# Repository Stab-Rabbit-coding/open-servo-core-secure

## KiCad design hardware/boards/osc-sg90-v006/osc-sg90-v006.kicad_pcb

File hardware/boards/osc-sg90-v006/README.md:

# OSC SG90 CH32

> ⚠️ **Designed, not spun. Pre-fabrication, pre-bringup.**
> This board has never been fabbed. Numbers and behaviour described below are **design intent**, not measured. The schematic and layout exist; firmware v2 now runs on the dev board (the bus transport is silicon-proven) but has never run on *this* board. Don't fab this without doing your own review first, and expect changes when bringup finally happens.

OpenServoCore swap board for SG90-class hobby servos. Compact, double-sided, designed to physically replace the factory PCB inside an SG90 case. CH32V006-based, single-wire TTL servo bus (osc-native protocol), drop-in mechanical fit.

## Overview

- **MCU** — CH32V006F8U6 (RISC-V, 48 MHz, 62 KB flash, 8 KB RAM).
- **Motor driver** — TI DRV8837 H-bridge (1.8 A peak, IN1/IN2 PWM).
- **LDO** — TPAP2210K-3.3, 3.3 V logic rail.
- **UART buffer** — SN74LVC1G07 open-drain for the half-duplex TTL bus.
- **Current shunt** — 25 mΩ, 1 % on the low side.
- **Power input** — 3.3-8.4 V (1S-2S LiPo) via the servo cable.
- **Debug** — 4-pad SWD interface for WCH-LinkE.
- **Position feedback** — existing servo potentiometer wiper.
- **Form factor** — 10 × 12.5 mm, double-sided assembly.
- **Secure element** — Microchip ECC204 (`U7`), 8-pad UDFN package, SWI on
  `PD6` [REF-SE-001]. **Placed on B.Cu with a generic 3D proxy model; 2
  residual real DRC clearance conflicts still open** — see
  [Secure element](#secure-element) below and `TODO.md` §7.8.

## Connectors

### Servo cable — J1 (1×3, through-hole pads)

Standard hobby-servo 3-wire pinout, but the signal pin carries half-duplex UART instead of PWM:

| Pin | Net    | Notes                                   |
| --- | ------ | --------------------------------------- |
| 1   | `VIN`  | 3.3-8.4 V (1S-2S LiPo).                 |
| 2   | `DATA` | Half-duplex UART, baud TBD by firmware. |
| 3   | `GND`  |                                         |

### Motor — J2 (2 wire pads)

Solder directly to the SG90 motor leads.

| Pad    | Net              |
| ------ | ---------------- |
| `OUTA` | Motor terminal A |
| `OUTB` | Motor terminal B |

### Potentiometer — J3 (3 pads)

Connects to the existing servo potentiometer.

| Pad    | Net          |
| ------ | ------------ |
| `+3V3` | Pot top rail |
| `VPOS` | Wiper        |
| `GND`  | Pot ground   |

### Debug — J4 (4 pads, 1.27 mm pitch)

Single-wire SWD for WCH-LinkE. Programmed via `wlink` / `probe-rs`. Firmware build instructions land when firmware v2 starts; until then there's nothing to flash.

| Pad | Net     |
| --- | ------- |
| 1   | `+3V3`  |
| 2   | `GND`   |
| 3   | `SWDIO` |
| 4   | `NC`    |

## Design intent

These are the targets the board was laid out around. None are measured.

- **Power architecture** — VIN routes to the DRV8837 directly; 3.3 V logic rail off the TPAP2210K LDO. Bulk capacitance is 2× 10 µF on VIN. PGND/GND joined at a single net tie.
- **Position sensing** — 12-bit ADC on `VPOS` with an RC filter (10 kΩ + 100 nF, fc ≈ 160 Hz) to suppress wiper noise. Sub-degree resolution is the design goal; actual precision waits on bringup and firmware oversampling.
- **Voltage sensing** — 20 kΩ / 10 kΩ dividers (ratio 0.333) on `VINS`, `VSNA`, `VSNB`. 8.4 V → 2.8 V at the ADC.
- **Current sensing** — 25 mΩ low-side shunt, sized for the DRV8837's ~1.76 A peak via `R_shunt ≈ 44 mV / I_stall`, so the hardware stall-detect path trips near the driver's max output. Raw V_shunt = 25 mV at 1 A; firmware sets ADC sampling, gain path, and software overcurrent threshold.
- **Communication** — single-wire half-duplex TTL servo bus (Dynamixel-TTL electrical layer; the wire protocol is [osc-native](../../../docs/osc-native-protocol.md)). The SN74LVC1G07 open-drain buffer enables bidirectional comms over the single `DATA` line. Bus rates: 0.5-3 Mbaud, default 1 M.
- **Protection** — PESD5V0L1UL TVS on `DATA`.

## Secure element

`U7` is a Microchip ECC204 (Value `ECC204-MAVCZ-T`), **8-pad UDFN** package,
100 kbps PWM Single-Wire Interface (SWI). Design of record:
[`docs/security-architecture.md`](../../../docs/security-architecture.md);
citations: [`REFERENCES.md`](../../../REFERENCES.md) `REF-SE-001`.

| Signal | Net       | Notes                                                                   |
| ------ | --------- | ----------------------------------------------------------------------- |
| `SI/O` | `SE_SWIO` | `PD6` on the MCU, one pull-up (`R10`) to `+3V3`.                        |
| `VCC`  | `+3V3`    | 0.1 µF decoupling (`C5`).                                               |
| `GND`  | `GND`     | Also `EP` (pin 9, exposed pad) — REF-SE-001 recommends tying it to GND. |

**Package: 8-pad UDFN, not 3-Lead Contact.** The 3-Lead Contact package
(6.5×2.5 mm) — the original choice — was confirmed by exhaustive search to
have **zero** clear placement anywhere on this board's routed copper. The
same real part's 8-pad UDFN (2×3 mm) does fit; see `TODO.md` §7.8 for the
search methodology and REFERENCES.md's "Removed / superseded citations" for
the supersession record.

**Placement — on B.Cu, real position, 2 residual real DRC conflicts open:**

- `U7 (101.7, 93.4)`, `R10 (103.3, 92.4)`, `C5 (103.0, 97.1)`, `C10 (103.7,
  95.015, −90)`, `RS1 (105.245002, 96.755, 90)`, `C2 (108.18, 91.08)`, all
  B.Cu — these are the final positions after re-verifying (and, for `RS1`/
  `C10`, wholesale-restoring) a round of manual GUI repositioning; see the
  data-integrity note below.
- `pcb drc --severity-all`: driven from 148 violations (induced by the
  original manual 3-Lead-Contact placement) down to 74 total / 27 new vs. a
  clean baseline. Of those 27: **2 are real** (`U7` pad 5 and `R10` pad 2
  each sit too close to one of `J4`'s three real through-hole pads —
  `(104.51, 92.0)` / `(103.06, 95.0)` / `(104.51, 98.0)`, confirmed via
  live Gerber `%TO.P,J4,n%` component-attribute flashes, not a stale-fill
  or duplicate-reference artifact; see `TODO.md` §7.8 for the placement
  math proving `U7` cannot clear both nearby `J4`/`J2` pads at once, and for
  fix options), 18 are `GND_POUR` zone-clearance findings now assessed as
  **likely real** (point-in-polygon tested against a live-exported Gerber's
  filled copper region — `U7`'s non-`GND` pads land inside the poured
  copper with no relief — though a live KiCad "Fill All Zones" + re-DRC is
  still the only fully conclusive check), and 3 are cosmetic
  `lib_footprint_mismatch` warnings (hand-authored footprint graphics vs. a
  full library re-import).
- `sch erc --severity-all`: 0 new violations (1 pre-existing, unrelated
  `DRV8837C` library-mismatch warning).
- **(BLOCKER for fab)** The 2 real conflicts need either further placement
  in a live KiCad GUI (this work was done headlessly, matching real pad
  geometry pulled from the raw `.kicad_pcb` and cross-checked against
  exported Gerbers — no substitute for actually seeing it), smaller pads
  still, or a justified DRC exclusion matching the `.kicad_pro`'s existing
  three exclusions for `J4`'s one-sided-TH quirk.

**Still open beyond placement:**

- `R10`'s pull-up value is `TBD`. The summary datasheet [REF-SE-001] has no
  application-circuit section and gives no recommended SWI pull-up; that
  needs the NDA datasheet or a CryptoAuthLib reference design (`TODO.md`
  §7.4).
- `ECC204-MAVCZ-T` is the **plain, unprovisioned** ordering code — a real
  example straight from [REF-SE-001] §7 (Product Identification System), not
  the fleet provisioning SKU. Whether fleet units ship pre-provisioned
  (TrustFLEX/TrustCUSTOM) or get provisioned from this raw part is still open
  (`TODO.md` §7.1/§7.5).
- The footprint,
  [`hardware/shared.pretty/ECC204_UDFN-8-1EP_L2.0-W3.0-P0.50-EP0.61x1.3mm.kicad_mod`](../../shared.pretty/ECC204_UDFN-8-1EP_L2.0-W3.0-P0.50-EP0.61x1.3mm.kicad_mod),
  deliberately uses smaller-than-generous pads (peripheral pads 0.5×0.25 mm,
  EP land 0.61 mm wide) to fit this board's real estate — sized to
  [REF-SE-001] §6.1's own terminal-to-exposed-pad `K = 0.20 mm` minimum, not
  arbitrary. Verify against a real part/stencil before fab.
- **Correction to a prior session's note:** an earlier pass here reported a
  "duplicate `J4` footprint / phantom pad" bug. That was wrong — it was a
  sign error in the reviewer's own PCB rotation math (`Rot(+θ)` used where
  `Rot(−θ)` was correct), not a board defect. `J4` is a single real
  footprint with three real through-hole pads; see `TODO.md` §7.8 for the
  corrected transform and its Gerber-based verification.
- **3D models added** for `U7`, `R10`, `C5` so KiCad's 3D viewer no longer
  shows bare footprints for these parts. `R10`/`C5` use the existing
  KiCad standard-library STEP models
  (`Resistor_SMD.3dshapes/R_0402_1005Metric.step`,
  `Capacitor_SMD.3dshapes/C_0402_1005Metric.step`), matching this board's
  existing convention for other passives. `U7` has no vendor-supplied
  3D model (Microchip does not publish one for the 8-pad UDFN), so it uses
  a generic dimensionally-accurate proxy generated from
  [REF-SE-001] §6.1's package dimensions (2.00 × 3.00 mm body, 0.55 mm
  height) — script and STL live at
  [`hardware/shared.3dshapes/ECC204_UDFN-8-1EP_L2.0-W3.0-P0.50.stl`](../../shared.3dshapes/ECC204_UDFN-8-1EP_L2.0-W3.0-P0.50.stl).
  Model references were added both to the library footprint
  (`shared.pretty/...kicad_mod`) and to each board instance directly (KiCad
  stores a full independent copy per instance — a library-only edit does
  not propagate to footprints already placed on this board). Confirmed no
  DRC regression from adding the models (74/9/27 unchanged); full visual
  confirmation in KiCad's 3D viewer was not achieved headlessly and should
  be spot-checked in the GUI before fab.
- **ERC/DRC verified with KiCad 10.0.3** (`kicad-cli` from the KiCad 10
  AppImage — the system-installed `kicad-cli` is 9.0.2 and cannot even load
  this file, since it's `generator_version "10.0"`).

## Assembly

Double-sided assembly, no vias-in-pads. Suitable for hot-plate / hot-air / IR reflow, or JLCPCB SMT. The board is 8-layer for routing density at this size.

## Mechanical fit

Designed to drop into a standard SG90 servo case:

- Motor leads solder to `OUTA` / `OUTB`.
- Pot wiper connects to `J3`.
- Servo cable connects to `J1`.
- Debug pads remain accessible through the case opening for bringup / reflashing.

Pad spacing for motor leads and debug pitch are still **to be confirmed against a physical case** when first boards arrive.

## License

Hardware files (schematic, layout, board files in this directory) are licensed under [CERN-OHL-P v2.0](../../../LICENSE-HARDWARE). See the [top-level README](../../../README.md#license) for the full licensing picture.

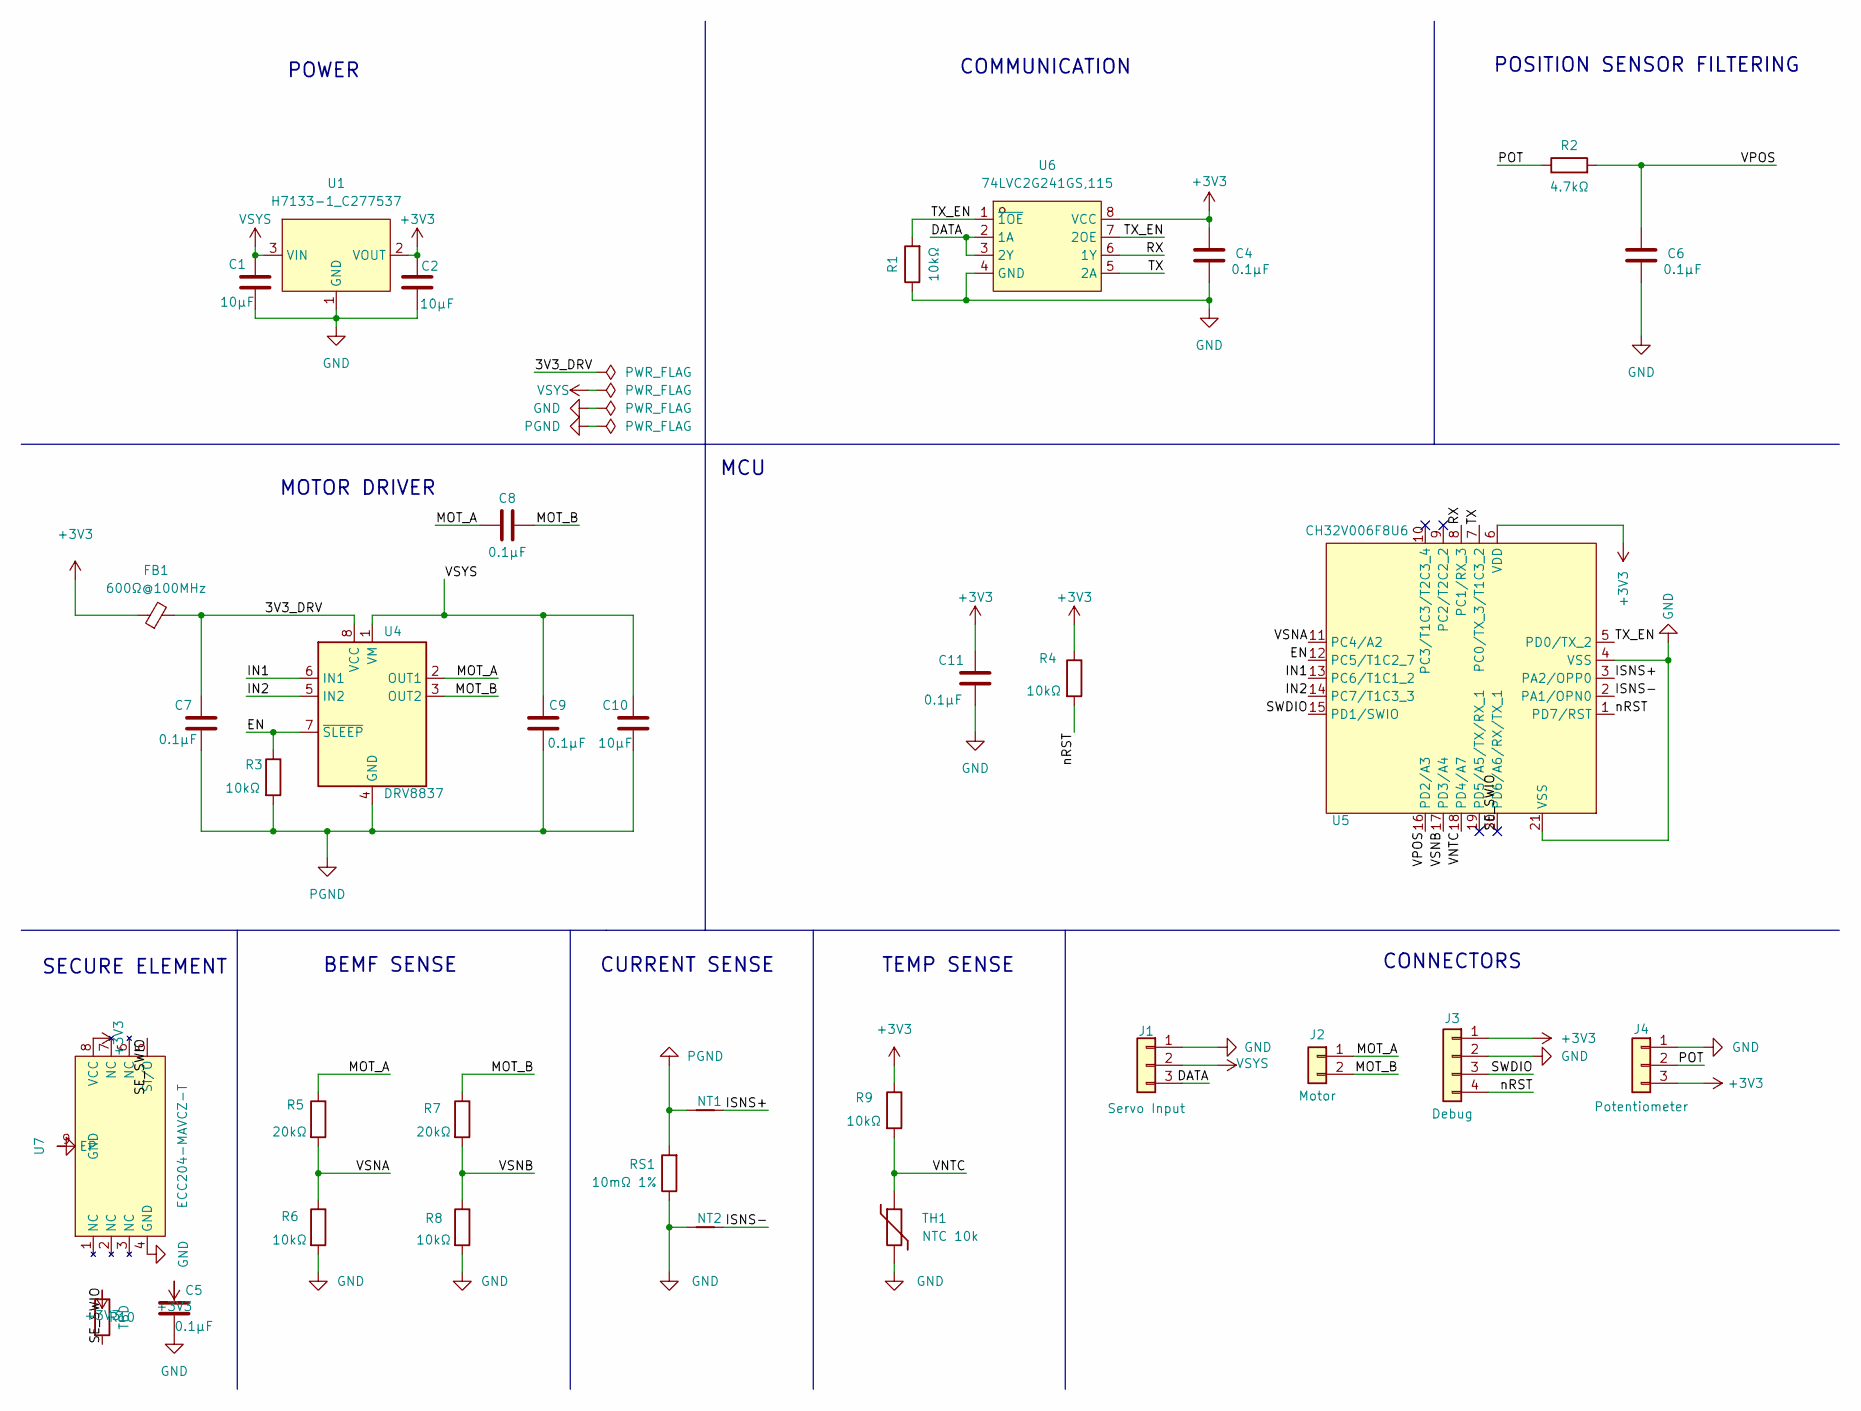
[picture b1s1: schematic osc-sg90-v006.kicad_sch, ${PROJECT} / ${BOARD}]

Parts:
C1, C2, C10: 10µF; C_0603_1608Metric; LCSC C96446
C4, C6, C7, C8, C9, C11: 0.1µF; C_0402_1005Metric; LCSC C1525
C5: 0.1µF; C_0402_1005Metric
FB1: 600Ω@100MHz; L_0402_1005Metric; LCSC C76884
J1: Servo Input; Servo_Output_Pads
J2: Motor; Motor_Wire_Pads
J3: Debug; Debug_Pads_1x4_P1.27mm
J4: Potentiometer; Pot_Wire_Pads
NT1, NT2: NetTie_2; NetTie-2_SMD_0.127mm
R1, R3, R4, R6, R8, R9: 10kΩ; R_0402_1005Metric; LCSC C25744
R2: 4.7kΩ; R_0402_1005Metric; LCSC C25900
R5, R7: 20kΩ; R_0402_1005Metric; LCSC C25765
R10: TBD; R_0402_1005Metric
RS1: 10mΩ 1%; R_0805_2012Metric; LCSC C163089
TH1: NTC 10k; R_0402_1005Metric; LCSC C77131
U1: H7133-1_C277537; SOT-23-3_L2.9-W1.3-P1.90-LS2.4-BR; LCSC Part C277537
U4: DRV8837; Texas_DSG0008A_WSON-8-1EP_2x2mm_P0.5mm_EP0.9x1.6mm; LCSC C39159
U5: CH32V006F8U6; UQFN-20_L3.0-W3.0-P0.40-BL-EP1.7; LCSC C42431288
U6: 74LVC2G241GS,115; XSON-8_L1.4-W1.0-P0.35-S0.55-BL; LCSC C548628
U7: ECC204-MAVCZ-T; ECC204_UDFN-8-1EP_L2.0-W3.0-P0.50-EP0.61x1.3mm

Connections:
+3V3: C2.1, C4.1, C5.1, C11.1, FB1.1, J3.1, J4.3, R4.1, R9.1, R10.1, U1.2 (VOUT), U5.6 (VDD), U6.8 (VCC), U7.8 (VCC)
/3V3_DRV: C7.1, FB1.2, U4.8 (VCC)
/DATA: J1.3, U6.2 (1A), U6.3 (2Y)
/EN: R3.1, U4.7 (~SLEEP), U5.12 (PC5/T1C2_7)
/IN1: U4.6 (IN1), U5.13 (PC6/T1C1_2)
/IN2: U4.5 (IN2), U5.14 (PC7/T1C3_3)
/ISNS+: NT1.1, U5.3 (PA2/OPP0)
/ISNS-: NT2.1, U5.2 (PA1/OPN0)
/MOT_A: C8.1, J2.1, R5.1, U4.2 (OUT1)
/MOT_B: C8.2, J2.2, R7.1, U4.3 (OUT2)
/POT: J4.2, R2.1
/RX: U5.8 (PC1/RX_3), U6.6 (1Y)
/SE_SWIO: R10.2, U5.20 (PD6/A6/RX/TX_1), U7.5 (SI/O)
/SWDIO: J3.3, U5.15 (PD1/SWIO)
/TX: U5.7 (PC0/TX_3/T1C3_2), U6.5 (2A)
/TX_EN: R1.2, U5.5 (PD0/TX_2), U6.1 (~1OE), U6.7 (2OE)
/VNTC: R9.2, TH1.1, U5.18 (PD4/A7)
/VPOS: C6.1, R2.2, U5.16 (PD2/A3)
/VSNA: R5.2, R6.1, U5.11 (PC4/A2)
/VSNB: R7.2, R8.1, U5.17 (PD3/A4)
/nRST: J3.4, R4.2, U5.1 (PD7/RST)
GND: C1.2, C2.2, C4.2, C5.2, C6.2, C11.2, J1.1, J3.2, J4.1, NT2.2, R1.1, R6.2, R8.2, RS1.1, TH1.2, U1.1 (GND), U5.4 (VSS), U5.21 (VSS), U6.4 (GND), U7.4 (GND), U7.9 (EP)
PGND: C7.2, C9.2, C10.2, NT1.2, R3.2, RS1.2, U4.4 (GND), U4.9 (GND)
VSYS: C1.1, C9.1, C10.1, J1.2, U1.3 (VIN), U4.1 (VM)

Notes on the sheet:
SECURE ELEMENT
POWER
MOTOR DRIVER
BEMF SENSE
CONNECTORS
TEMP SENSE
CURRENT SENSE
COMMUNICATION
MCU
POSITION SENSOR FILTERING

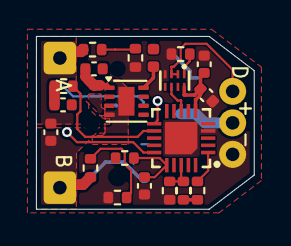
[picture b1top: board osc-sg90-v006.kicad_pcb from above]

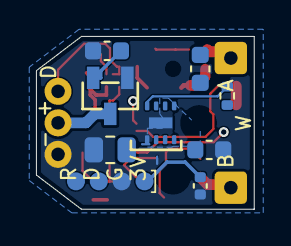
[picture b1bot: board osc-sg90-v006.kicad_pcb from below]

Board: 4 copper layers, 12.1 x 9.6 mm, 34 parts (11 on the bottom side), 24 nets.
